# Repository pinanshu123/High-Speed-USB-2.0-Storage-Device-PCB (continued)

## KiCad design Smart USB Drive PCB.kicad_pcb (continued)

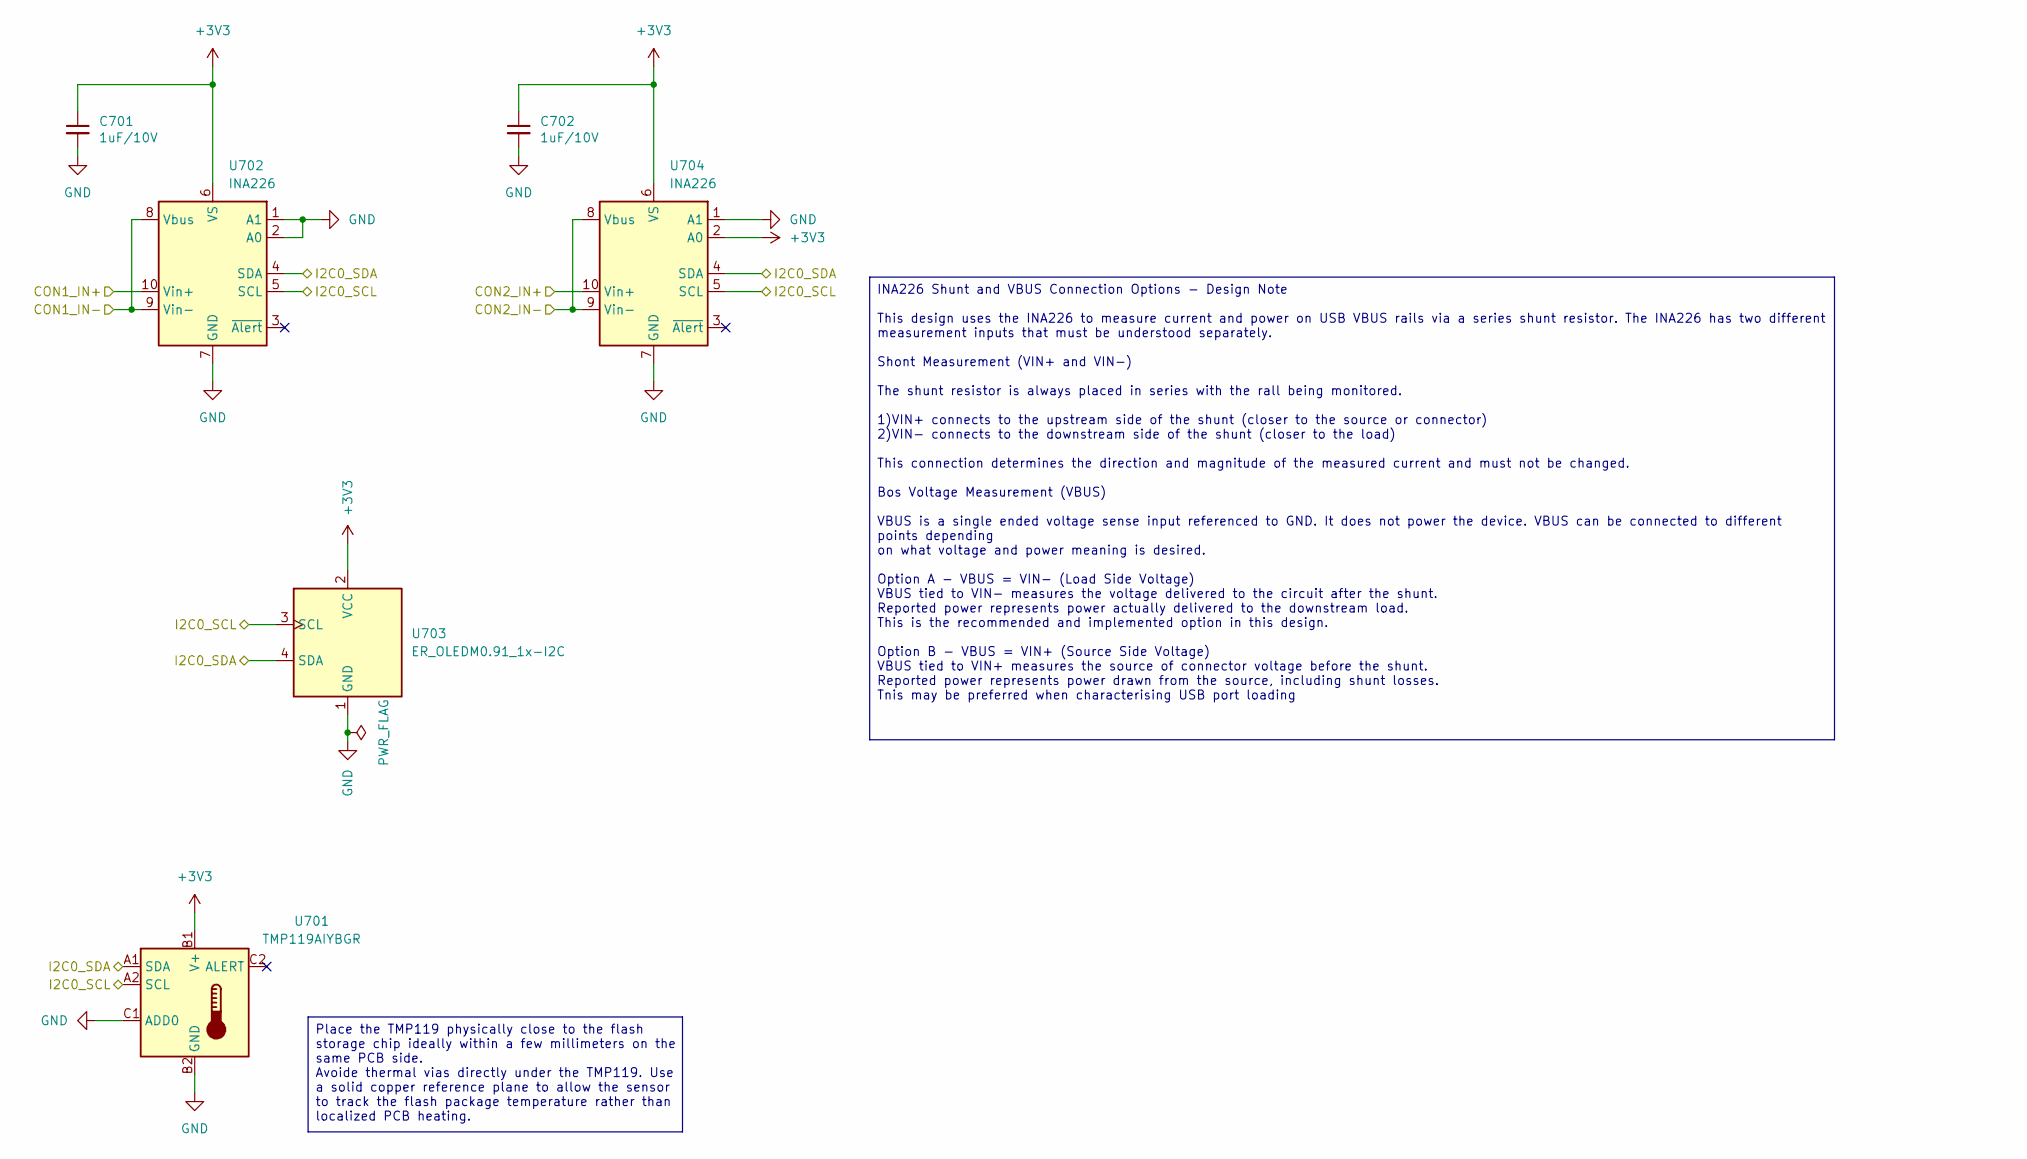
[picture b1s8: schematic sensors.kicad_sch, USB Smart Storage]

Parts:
C701, C702: 1uF/10V; C_0402_1005Metric
U701: TMP119AIYBGR; Texas_DSBGA-6_0.95x1.488mm_Layout2x3_P0.4mm
U702, U704: INA226; TSSOP-10_3x3mm_P0.5mm
U703: ER_OLEDM0.91_1x-I2C; SSD1306-0.91-OLED-4pin-128x32

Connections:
+3V3: C701.1, C702.1, U701.B1 (V+), U702.6 (VS), U703.2 (VCC), U704.2 (A0), U704.6 (VS); also elsewhere on the board
/RP2040/I2C0_SCL: U701.A2 (SCL), U702.5 (SCL), U703.3 (SCL), U704.5 (SCL); also elsewhere on the board
/RP2040/I2C0_SDA: U701.A1 (SDA), U702.4 (SDA), U703.4 (SDA), U704.4 (SDA); also elsewhere on the board
/VBUS_MCU_IN+: U704.10 (Vin+); also elsewhere on the board
/VBUS_MCU_IN-: U704.8 (Vbus), U704.9 (Vin-); also elsewhere on the board
/VBUS_STORAGE_IN+: U702.10 (Vin+); also elsewhere on the board
/VBUS_STORAGE_IN-: U702.8 (Vbus), U702.9 (Vin-); also elsewhere on the board
GND: C701.2, C702.2, U701.B2 (GND), U701.C1 (ADD0), U702.1 (A1), U702.2 (A0), U702.7 (GND), U703.1 (GND), U704.1 (A1), U704.7 (GND); also elsewhere on the board

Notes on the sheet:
Place the TMP119 physically close to the flash storage chip ideally within a few millimeters on the same PCB side. Avoide thermal vias directly under the TMP119. Use a solid copper reference plane to allow the sensor to track the flash package temperature rather than localized PCB heating.
INA226 Shunt and VBUS Connection Options - Design Note This design uses the INA226 to measure current and power on USB VBUS rails via a series shunt resistor. The INA226 has two different measurement inputs that must be understood separately. Shont Measurement (VIN+ and VIN-) The shunt resistor is 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

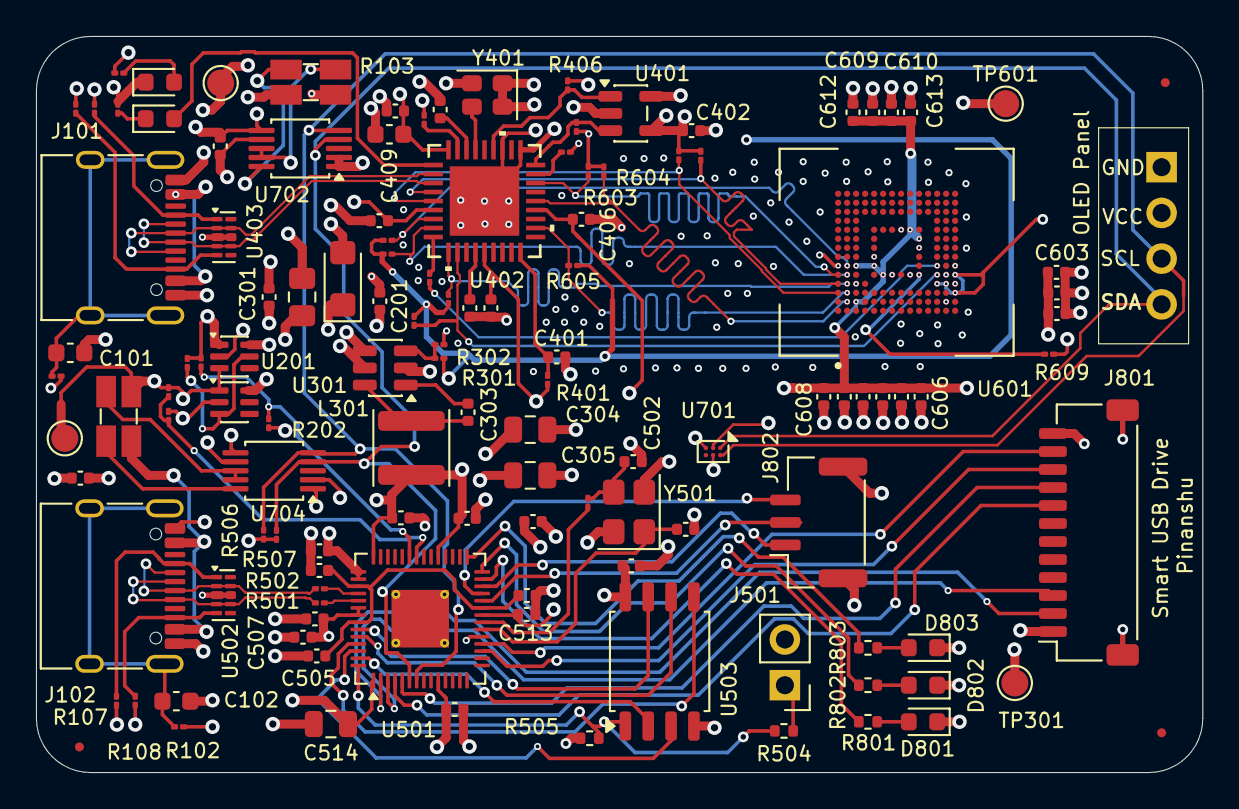
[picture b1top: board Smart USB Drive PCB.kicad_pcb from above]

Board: 4 copper layers, 64.8 x 40.9 mm, 122 parts (0 on the bottom side), 80 nets.

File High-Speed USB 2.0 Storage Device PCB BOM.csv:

Designator*,Quantity*,Manufacturer Part Number*,Manufacturer,Package/Footprint,Description,Procurement Type,Customer Note
"C101,C102",2,GRM1885C2A222JA01D,Murata Electronics,0603 (1608 Metric),2.2nF 100V,,2.2nF ±5% 100V C0G/NP0
"C201,C303,C403,C404,C602,C612",6,GRM155R61A105KE15D,Murata Electronics,0402 (1005 Metric),1uF 10V,,1uF ±10% 10V X5R
"C301,C405,C406,C407,C408,C601,C608,C609,C610,C611",10,GRM155R71A104KA01D,Murata Electronics,0402 (1005 Metric),0.1uF 10V,,0.1uF ±10% 10V X7R
C302,1,GRM21BR61A226ME44L,Murata Electronics,0805 (2012 Metric),22uF 10V,,22uF ±20% 10V X5R
"C304,C305",2,GRM21BR61A226ME44L,Murata Electronics,0805 (2012 Metric),22uF 10V,,22uF ±20% 10V X5R
C401,1,GRM155R71A104KA01D,Murata Electronics,0402 (1005 Metric),0.1uF/ 10V,,0.1uF ±10% 10V X7R
C402,1,GRM155R71A104KA01D,Murata Electronics,0402 (1005 Metric),100nF 10V,,100nF = 0.1uF ±10% 10V X7R
C409,1,CC0603KRX5R6BB475,YAGEO,0603 (1608 Metric),4.7uF 10V,,4.7uF ±10% 10V X5R
C501,1,GRM1555C1H150JA01D,Murata Electronics,0402 (1005 Metric),15p/ 10V,,15pF ±5% 50V C0G/NP0
C502,1,GRM1555C1H150JA01D,Murata Electronics,0402 (1005 Metric),15p 10V,,15pF ±5% 50V C0G/NP0
"C503,C504",2,GRM1555C1H150JA01D,Murata Electronics,0402 (1005 Metric),15pF 10V,,15pF ±5% 50V C0G/NP0
"C505,C507,C509",3,GRM155R61A105KE15D,Murata Electronics,0402 (1005 Metric),1u / 10V,,1uF ±10% 10V X5R
"C506,C508,C510,C511,C512,C513",6,GRM155R71H102KA01D,Murata Electronics,0402 (1005 Metric),1n / 10V,,1nF ±10% 50V X7R
C514,1,CC0805KRX5R6BB106,YAGEO,0805 (2012 Metric),10u / 10V,,10uF ±10% 10V X5R
C515,1,GRM155R71A104KA01D,Murata Electronics,0402 (1005 Metric),100n,,100nF 10V X7R selected
"C603,C604,C605,C606,C607,C613",6,GRM155R61A225KE95D,Murata Electronics,0402 (1005 Metric),2.2uF 10V,,2.2uF ±10% 10V X5R
"C701,C702",2,GRM155R61A105KE15D,Murata Electronics,0402 (1005 Metric),1uF/10V,,1uF ±10% 10V X5R
D301,1,SMF5V0A-E3-08,Vishay,SMF (DO-219AB),SMF5V0A,,"5V TVS diode, full orderable MPN"
"D302,D401",2,LTST-C190KRKT,Lite-On,0603 (1608 Metric),LED RED,,"Red LED, matches schematic value LED RED"
"D801,D802,D803",3,LTST-C190KGKT,Lite-On,0603 (1608 Metric),LED,,VERIFY | Original BOM says only LED; selected GREEN 0603 LED as an explicit assumption. Change MPN if a different color is intended.
"J101,J102",2,U262-161N-4BVC11,XKB Connection,"USB-C receptacle, 16P, right-angle",USB_C_Receptacle_USB2.0_16P,,Corrected actual manufacturer MPN; KiCad footprint name uses U262-16XN-4BVC11.
J501,1,61300211121,Würth Elektronik,"THT 1x2, 2.54mm vertical",Conn_01x02,,Concrete part selected for generic 2-pin 2.54mm header.
J801,1,SM12B-SRSS-TB(LF)(SN),JST,"SH 1x12, 1.00mm, right-angle SMD",Conn_01x12,,Full orderable JST MPN.
J802,1,SM03B-GHS-TB(LF)(SN),JST,"GH 1x3, 1.25mm, right-angle SMD",Conn_01x03,,Full orderable JST MPN.
L301,1,WPN4020H2R2MT,Sunlord,SMD 4.0x4.0x2.0mm,"2.2uH/4,3A",,VERIFY | 2.2uH / 4.3A exact electrical match. Your KiCad footprint is named SWPA4020S; verify pad geometry against WPN4020H datasheet before fabrication.
"R101,R102",2,RC0100FR-071ML,YAGEO,01005 (0402 Metric),1M/1%,,"1MΩ ±1%, 1/32W"
"R103,R104",2,L4CL1206LR002FNR,Littelfuse,"1206 (3216 Metric), 4-terminal",2m/1%,,"VERIFY | 2mΩ ±1% current-sense resistor. Original footprint is Ohmite LVK12, but LVK12 starts at 10mΩ; verify/change PCB footprint to the Littelfuse 4-terminal land pattern before ordering."
"R105,R106",2,RC0100FR-075K49L,YAGEO,01005 (0402 Metric),5.5K/1%,,VERIFY | Selected 5.49kΩ ±1% E96 value as the practical exact part for schematic value 5.5K/1%.
"R107,R108",2,RC0100FR-072ML,YAGEO,01005 (0402 Metric),2M/1%,,"2MΩ ±1%, 1/32W"
"R201,R203,R205,R301",4,RC0100FR-07100KL,YAGEO,01005 (0402 Metric),100K/1%,,"100kΩ ±1%, 1/32W"
"R202,R204",2,RC0100FR-07150KL,YAGEO,01005 (0402 Metric),150K/1%,,"150kΩ ±1%, 1/32W"
R302,1,RC0100FR-0722K1L,YAGEO,01005 (0402 Metric),22.1K/1%,,"22.1kΩ ±1%, 1/32W"
"R303,R503",2,RC0100FR-071KL,YAGEO,01005 (0402 Metric),1K/1%,,"1kΩ ±1%, 1/32W"
R401,1,RC0100FR-071ML,YAGEO,01005 (0402 Metric),1M 1%,,"1MΩ ±1%, 1/32W"
R402,1,RC0100FR-0712KL,YAGEO,01005 (0402 Metric),12K 1%,,"12kΩ ±1%, 1/32W"
R403,1,RC0100FR-07330RL,YAGEO,01005 (0402 Metric),330 1%,,"330Ω ±1%, 1/32W"
"R404,R405,R406",3,RC0100FR-0710KL,YAGEO,01005 (0402 Metric),10K 1%,,"10kΩ ±1%, 1/32W"
"R501,R502",2,RC0100FR-0727R4L,YAGEO,01005 (0402 Metric),27.4/1%,,"27.4Ω ±1%, 1/32W"
R504,1,RC0402FR-071KL,YAGEO,0402 (1005 Metric),1k/1%,,"1kΩ ±1%, 1/16W"
"R506,R507",2,RC0100FR-074K7L,YAGEO,01005 (0402 Metric),4.7k/1%,,"4.7kΩ ±1%, 1/32W"
"R601,R602,R603,R604,R605,R606,R607,R608",8,RC0100FR-0747KL,YAGEO,01005 (0402 Metric),47K/1%,,"47kΩ ±1%, 1/32W"
"R609,R611",2,RC0100FR-0710KL,YAGEO,01005 (0402 Metric),10K/1%,,"10kΩ ±1%, 1/32W"
R610,1,RC0100FR-0722RL,YAGEO,01005 (0402 Metric),22/1%,,"22Ω ±1%, 1/32W"
"R801,R802,R803",3,RC0402FR-071KL,YAGEO,0402 (1005 Metric),1K,,"1kΩ ±1%, 1/16W"
"U201,U202",2,LM66100DCKR,Texas Instruments,SC70-6 / SOT-363,LM66100DCK,,Full tape-and-reel orderable MPN.
U301,1,SY8253ADC,Silergy,TSOT-23-6,SY8253-ADC,,VERIFY | Exact device selected from value SY8253-ADC. Note: the Datasheet URL in your KiCad BOM points to a TI LM2734 and is wrong; replace it with the Silergy datasheet.
U401,1,AT24CS04-STUM-T,Microchip Technology,SOT-23-5,AT24CS04-STUM,,OK / MANUAL SOURCE | Valid full orderable MPN. NextPCB auto-matcher previously did not find it; keep exact MPN for manual sourcing.
U402,1,USB2244-AEZG-06,Microchip Technology,"QFN-36, 6x6mm",USB2244-AEZG-06,,OK / MANUAL SOURCE | Valid commercial-temperature MPN. NextPCB auto-matcher previously did not find it; do not invent a suffix.
"U403,U502",2,D3V3XA4B10LP-7,Diodes Incorporated,U-DFN2510-10 (1.0x2.5mm),D3V3XA4B10LP,,Full tape-and-reel MPN.
U501,1,RP2040,Raspberry Pi,"QFN-56, 7x7mm",RP2040,,RP2040 MCU.
U503,1,W25Q128JVSIQ,Winbond,"SOIC-8, 208mil",W25Q128JVS,,Full 12-character orderable MPN corresponding to W25Q128JVS in your BOM.
U601,1,MTFC64GAPALBH-IT,Micron Technology,"BGA-153, 11.5x13mm",MTFC64GAPALBH-IT,,"OBSOLETE | Exact original MPN, but Micron lists this eMMC as obsolete. Use exact part for prototype only if sourcing is acceptable; redesign to a current compatible eMMC for production."
U701,1,TMP119AIYBGR,Texas Instruments,DSBGA-6,TMP119AIYBGR,,Exact original MPN.
"U702,U704",2,INA226AIDGSR,Texas Instruments,"VSSOP-10, 3x3mm, 0.5mm pitch",INA226,,Selected exact VSSOP-10 orderable version matching footprint.
U703,1,ER-OLEDM0.91-1B-I2C,EastRising / BuyDisplay,"0.91in 128x32 OLED module, 4-pin I2C",ER_OLEDM0.91_1x-I2C,,VERIFY | Original value omitted the display color. Selected BLUE (-1B-) variant as an assumption; change to -1W- if white is intended.
Y401,1,SG-210STF 24.0000ML0,Epson,2.5x2.0mm 4-SMD oscillator,SG-210STF,,VERIFY | 24MHz selected because Y401 is the USB2244 reference oscillator and USB2244 uses a 24MHz reference. Confirm schematic net/function before ordering.
Y501,1,ABM8-272-T3,Abracon,3.2x2.5mm 4-SMD crystal,Crystal_GND24,,VERIFY | 12MHz crystal selected for RP2040; your 15pF load-cap network is consistent with ~10pF crystal load. Confirm schematic before ordering.
